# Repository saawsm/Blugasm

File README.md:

# Blugasm - A Bluetooth enabled Nogasm

This project aims to predict and detect orgasms by using a pressure sensor (and optionally, additional I2C sensors such as SpO2 and/or GSR sensor) while controlling a vibrator.

The original design and concept comes from the [nogasm](https://github.com/nogasm/nogasm). It improves upon it by making it battery operated and Bluetooth enabled, thanks to the ESP-32 microcontroller.

## Acknowledgements
The design of this board was inspired/based off the [nogasm board](https://github.com/nogasm/nogasm).

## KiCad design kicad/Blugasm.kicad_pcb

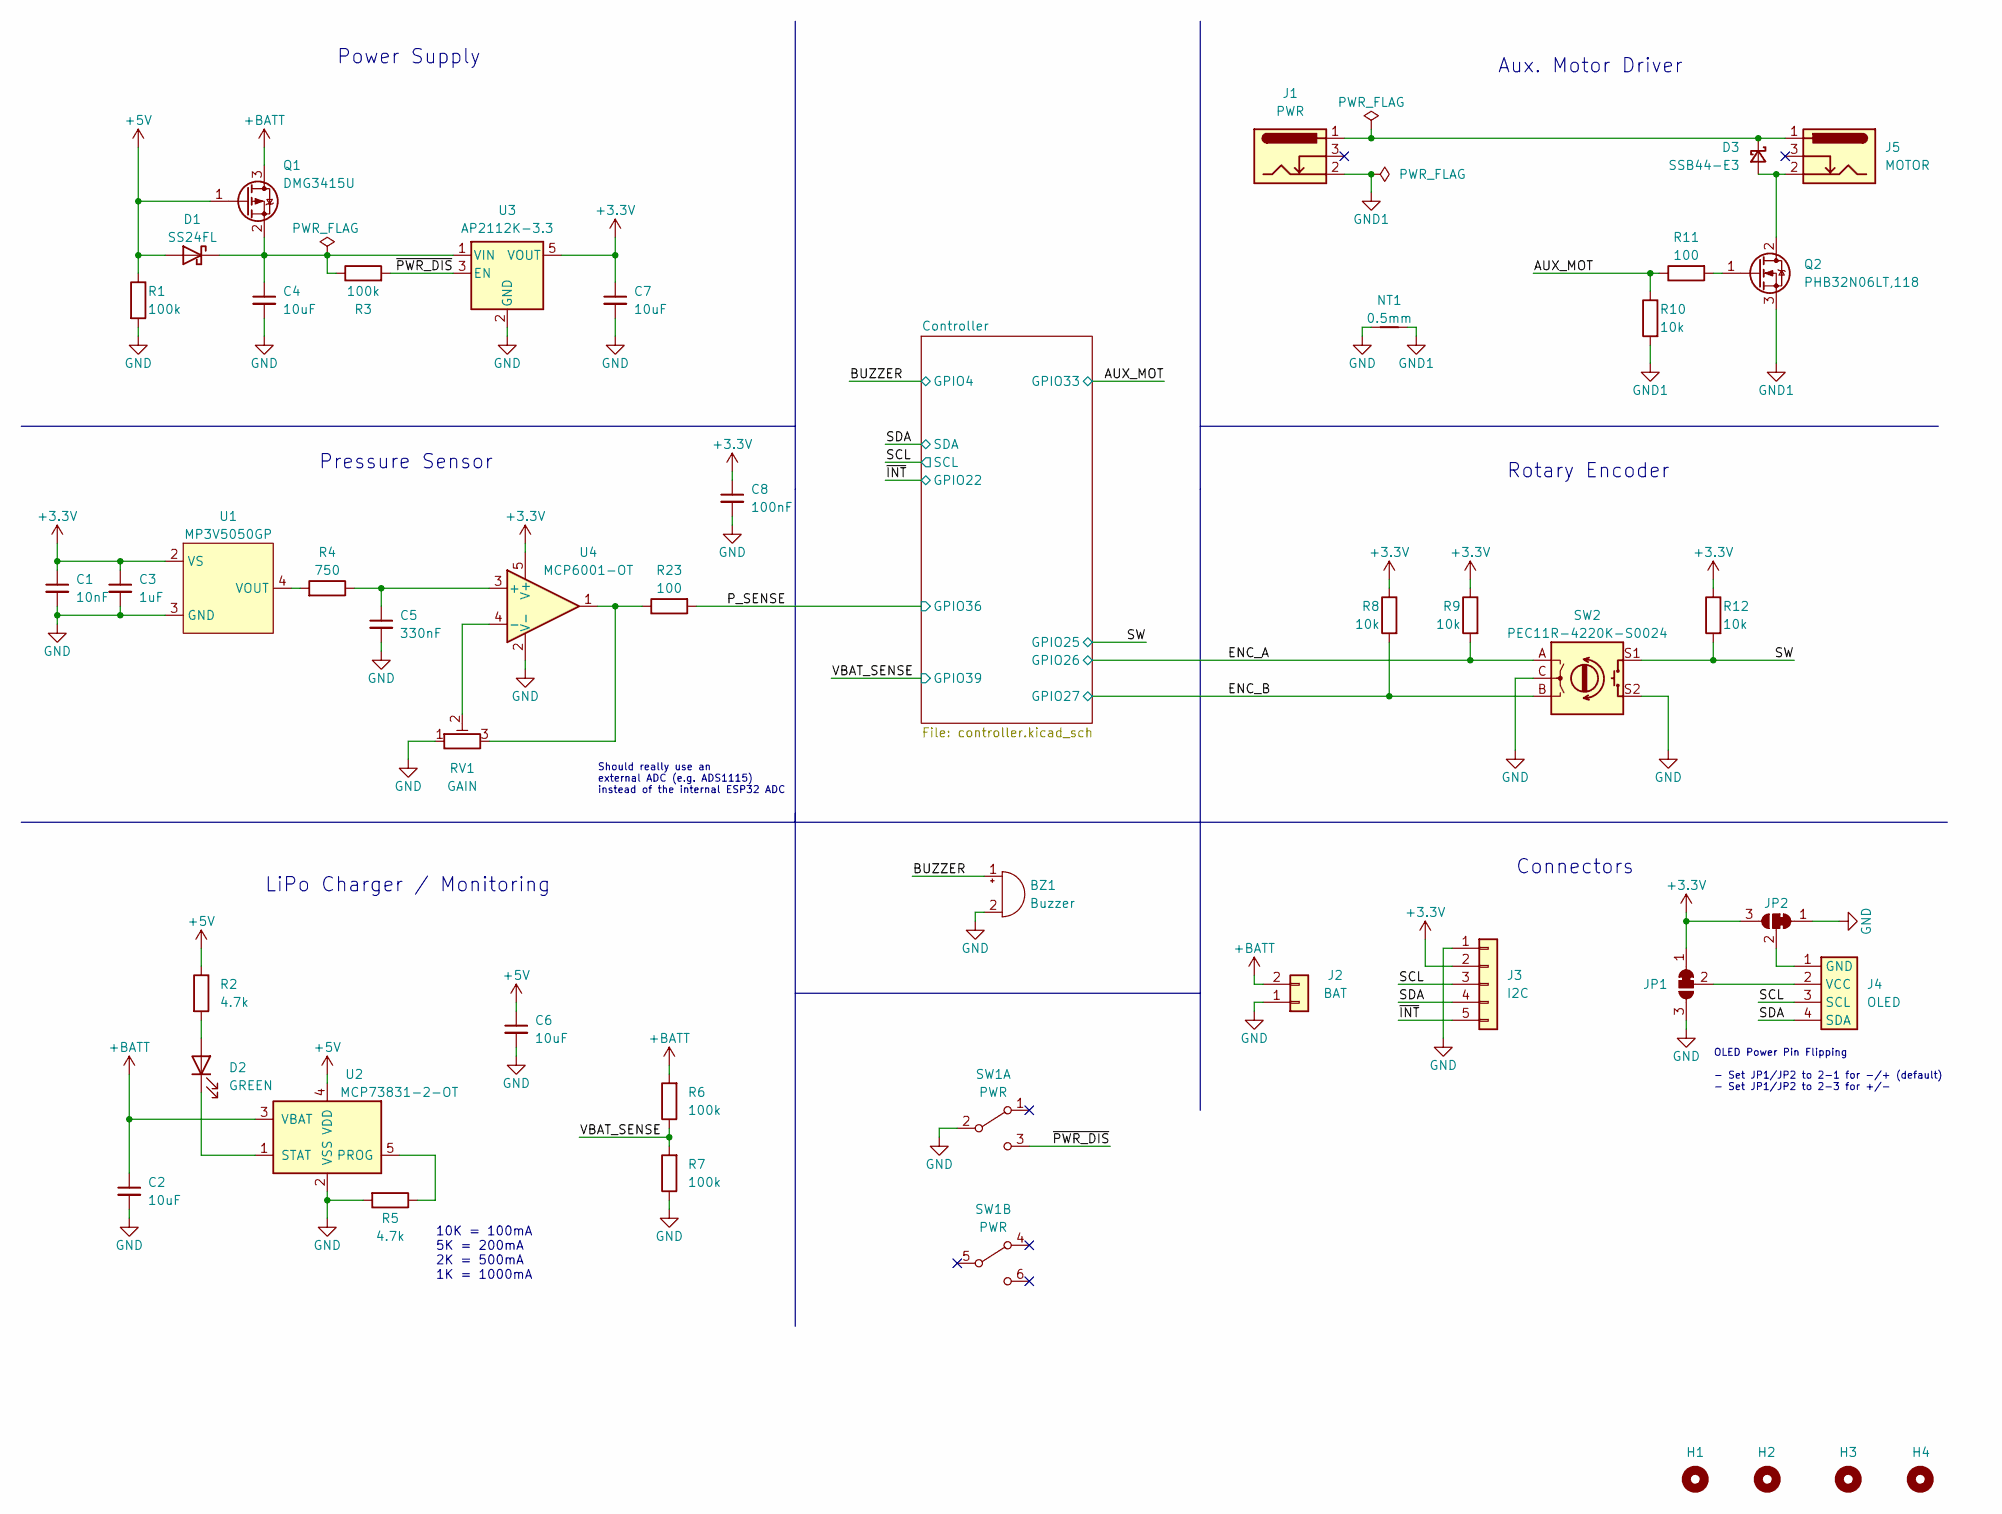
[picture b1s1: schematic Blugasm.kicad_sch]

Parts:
BZ1: Buzzer; Buzzer_12x9.5RM7.6; MPN IE122303-1; MOUSER 497-IE122303-1
C1: 10nF; C_0603_1608Metric; MPN CL10B103KB8NNNC; LCSC C1589
C2, C4, C6, C7: 10uF; C_0603_1608Metric; MPN CL10A106MA8NRNC; LCSC C96446
C3: 1uF; C_0603_1608Metric; MPN CL10B105KA8NFNC; LCSC C307479
C5: 330nF; C_0603_1608Metric; MPN CL10B334KO8NNNC; LCSC C159798
C8: 100nF; C_0603_1608Metric; MPN CL10B104KB8NNWC; LCSC C1591
D1: SS24FL; D_SOD-123F; MPN SS24FL; LCSC C894433
D2: GREEN; LED_0603_1608Metric; MPN 150060VS75000; MOUSER 710-150060VS75000
D3: SSB44-E3; D_SMB; MPN SSB44-E3/52T; LCSC C466999
H1, H2, H3, H4: MountingHole; MountingHole_2.2mm_M2
J1: PWR; BarrelJack_CUI_PJ-102AH_Horizontal; MPN PJ-102AH; MOUSER 490-PJ-102AH
J2: BAT; JST_PH_B2B-PH-K_1x02_P2.00mm_Vertical
J3: I2C; PinHeader_1x05_P2.54mm_Horizontal
J4: OLED; OLED_I2C
J5: MOTOR; BarrelJack_CUI_PJ-102AH_Horizontal; MPN PJ-102AH; MOUSER 490-PJ-102AH
JP1, JP2: SolderJumper_3_Bridged12; SolderJumper-3_P1.3mm_Bridged12_Pad1.0x1.5mm_NumberLabels
NT1: 0.5mm; NetTie-2_SMD_Pad0.5mm
Q1: DMG3415U; SOT-23; MPN DMG3415UQ-7; LCSC C459537
Q2: PHB32N06LT,118; TO-263-3_TabPin2; MPN PHB32N06LT,118; LCSC C552626
R1, R3, R6, R7: 100k; R_0603_1608Metric; MPN RC0603FR-07100KL; LCSC C14675
R2, R5: 4.7k; R_0603_1608Metric; MPN RC0603FR-074K7L; LCSC C99782
R4: 750; R_0603_1608Metric; MPN RC0603FR-07750RL; LCSC C114635
R8, R9, R10, R12: 10k; R_0603_1608Metric; MPN RC0603FR-0710KL; LCSC C98220
R11, R23: 100; R_0603_1608Metric; MPN RC0603FR-07100RL; LCSC C105588
RV1: GAIN; ST-4EB; MPN ST-4ETB103; LCSC C2922095
SW1: PWR; SW_E-Switch_EG2219_DPDT_Angled; MPN EG2219; MOUSER 612-EG2219
SW2: PEC11R-4220K-S0024; Rotary_Encoder_Switched_PEC11R; MPN PEC11R-4220K-S0024; MOUSER 652-PEC11R-4220K-S24
U1: MP3V5050GP; MP3V5050; MPN MP3V5050GP; MOUSER 841-MP3V5050GP
U2: MCP73831-2-OT; SOT-23-5; MPN MCP73831T-2ACI/OT; LCSC C424093
U3: AP2112K-3.3; SOT-23-5; MPN AP2112K-3.3TRG1; LCSC C51118
U4: MCP6001-OT; SOT-23-5; MPN MCP6001RT-I/OT; MOUSER 579-MCP6001RT-I/OT

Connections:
+3.3V: C1.1, C3.1, C7.1, C8.1, J3.2, JP1.1 (A), JP2.3 (B), R8.1, R9.1, R12.1, U1.2 (VS), U3.5 (VOUT), U4.5 (V+); also elsewhere on the board
+5V: C6.1, D1.2 (A), Q1.1 (G), R1.1, R2.1, U2.4 (VDD); also elsewhere on the board
+BATT: C2.1, J2.2, Q1.3 (D), R6.2, U2.3 (VBAT)
/AUX_MOT: R10.1, R11.1; also elsewhere on the board
/BUZZER: BZ1.1 (-); also elsewhere on the board
/ENC_A: R9.2, SW2.A; also elsewhere on the board
/ENC_B: R8.2, SW2.B; also elsewhere on the board
/P_SENSE: R23.2; also elsewhere on the board
/SCL: J3.3, J4.3 (SCL); also elsewhere on the board
/SDA: J3.4, J4.4 (SDA); also elsewhere on the board
/SW: R12.2, SW2.S1; also elsewhere on the board
/VBAT_SENSE: R6.1, R7.2; also elsewhere on the board
/~INT: J3.5; also elsewhere on the board
/~PWR_DIS: R3.2, SW1.3 (C), U3.3 (EN)
GND: BZ1.2 (+), C1.2, C2.2, C3.2, C4.2, C5.2, C6.2, C7.2, C8.2, J2.1, J3.1, JP1.3 (B), JP2.1 (A), NT1.1, R1.2, R5.2, R7.1, RV1.1, SW1.2 (B), SW2.C, SW2.S2, U1.3 (GND), U2.2 (VSS), U3.2 (GND), U4.2 (V-); also elsewhere on the board
GND1: J1.2, NT1.2, Q2.3 (S), R10.2
unnamed: C4.1, D1.1 (K), Q1.2 (S), R3.1, U3.1 (VIN)
unnamed: C5.1, R4.1, U4.3 (+)
unnamed: D2.1 (K), U2.1 (STAT)
unnamed: D2.2 (A), R2.2
unnamed: D3.1 (K), J1.1, J5.1
unnamed: D3.2 (A), J5.2, Q2.2 (D)
unnamed: J4.1 (GND), JP2.2 (C)
unnamed: J4.2 (VCC), JP1.2 (C)
unnamed: Q2.1 (G), R11.2
unnamed: R4.2, U1.4 (VOUT)
unnamed: R5.1, U2.5 (PROG)
unnamed: R23.1, RV1.3, U4.1
unnamed: RV1.2, U4.4 (-)

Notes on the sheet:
Should really use an external ADC (e.g. ADS1115) instead of the internal ESP32 ADC
Aux. Motor Driver
Connectors
OLED Power Pin Flipping - Set JP1/JP2 to 2-1 for -/+ (default) - Set JP1/JP2 to 2-3 for +/-
10K = 100mA 5K = 200mA 2K = 500mA 1K = 1000mA
Rotary Encoder
Pressure Sensor
Power Supply
LiPo Charger / Monitoring

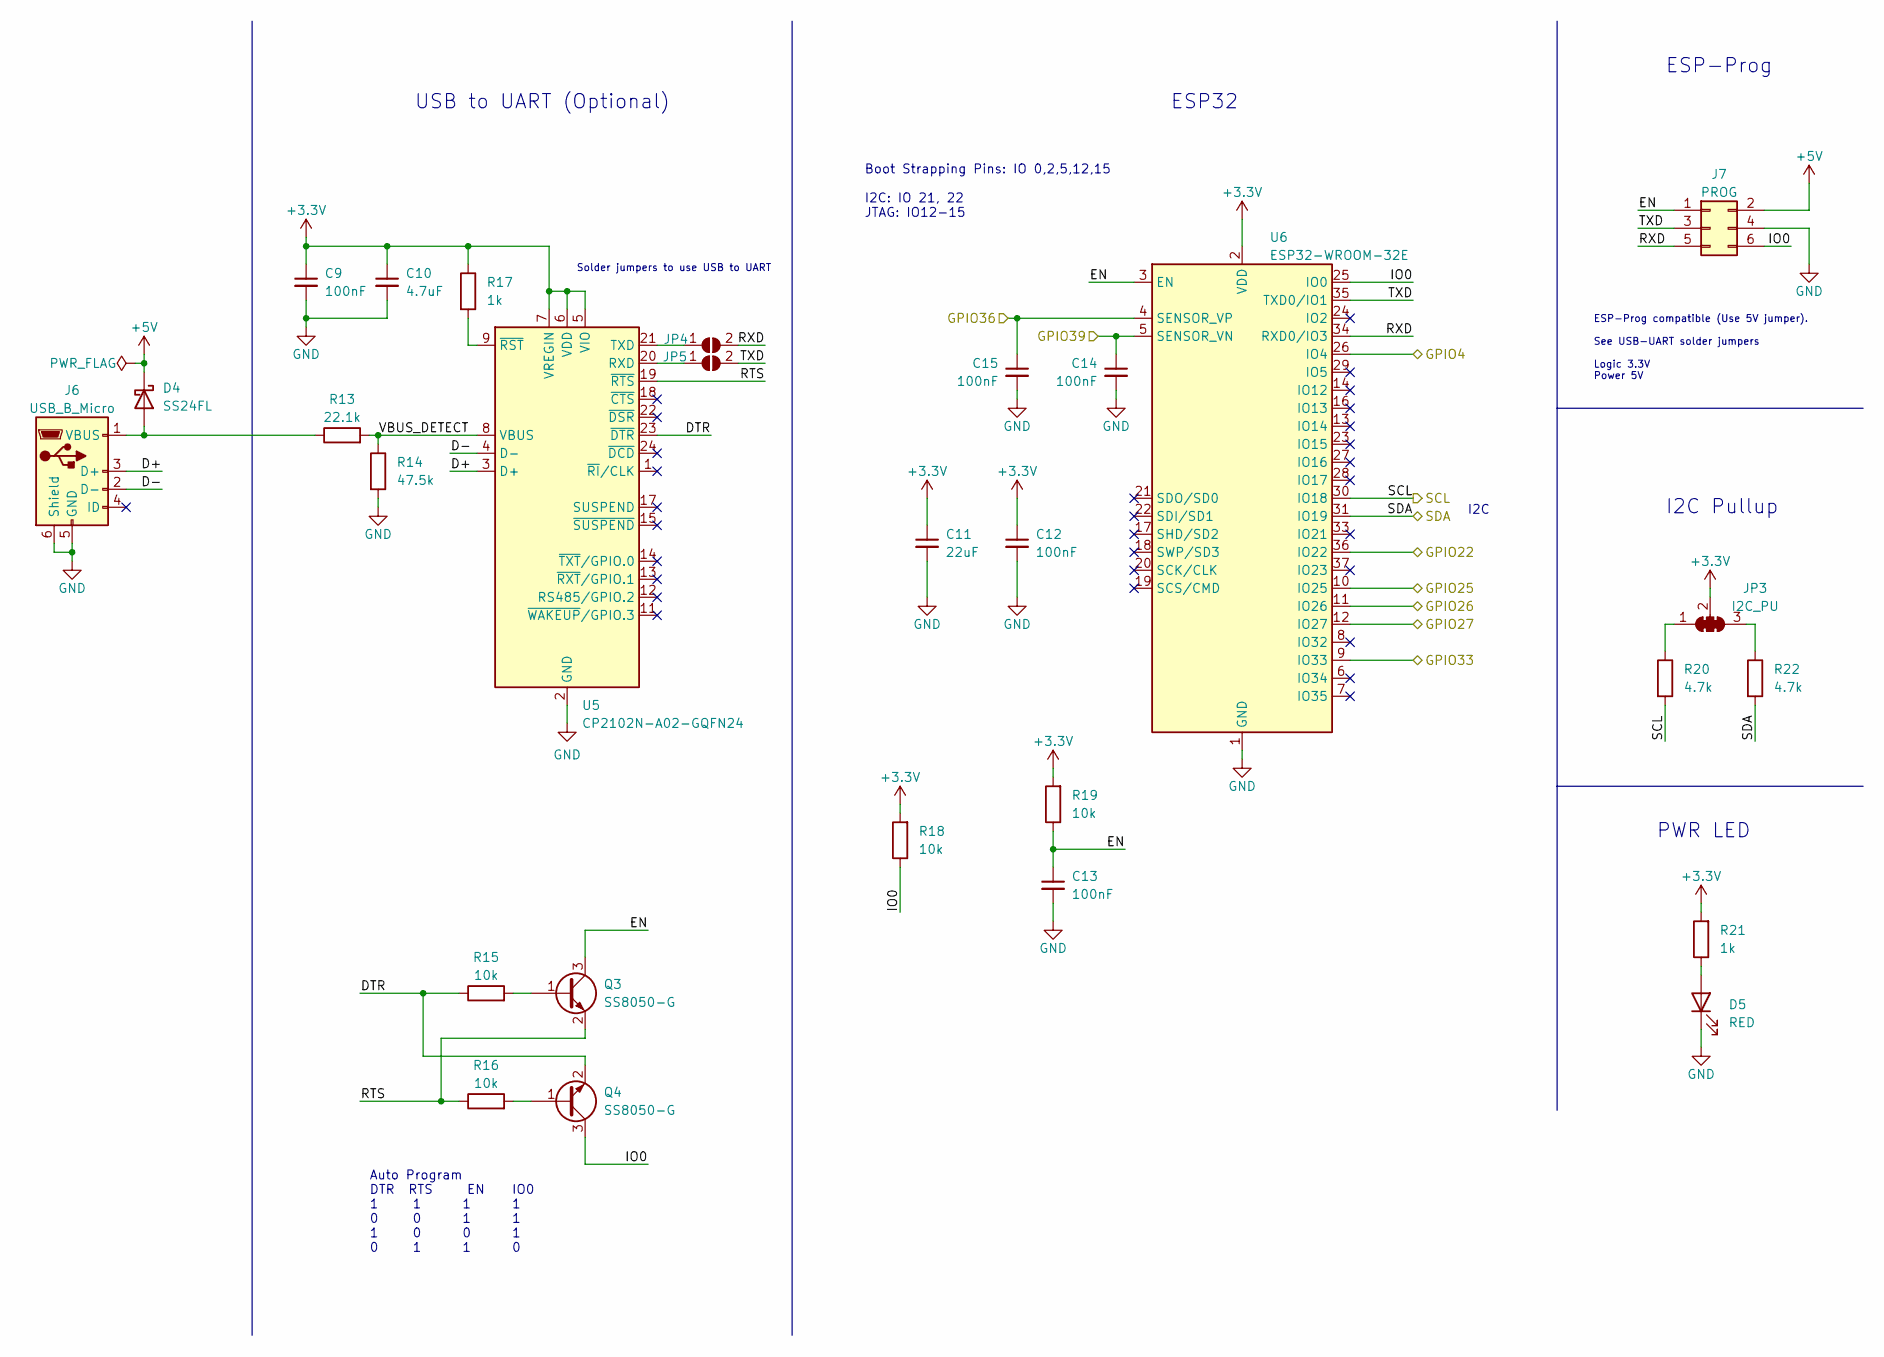
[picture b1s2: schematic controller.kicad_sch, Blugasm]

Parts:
C9, C12, C13, C14, C15: 100nF; C_0603_1608Metric; MPN CL10B104KB8NNWC; LCSC C1591
C10: 4.7uF; C_0603_1608Metric; MPN CL10A475KQ8NNWC; LCSC C3849923
C11: 22uF; C_0603_1608Metric; MPN CL10A106MA8NRNC; LCSC C96446
D4: SS24FL; D_SOD-123F; MPN SS24FL; LCSC C894433
D5: RED; LED_0603_1608Metric; MPN 150060RS75000; MOUSER 710-150060RS75000
J6: USB_B_Micro; USB_Micro-B_GCT_USB3076-30-A; MPN USB3076-30-A; MOUSER 640-USB3076-30-A
J7: PROG; IDC-Header_2x03_P2.54mm_Vertical
JP3: I2C_PU; SolderJumper-3_P1.3mm_Bridged123_Pad1.0x1.5mm_NumberLabels
JP4: UART_TXD; SolderJumper-2_P1.3mm_Open_RoundedPad1.0x1.5mm
JP5: UART_RXD; SolderJumper-2_P1.3mm_Open_RoundedPad1.0x1.5mm
Q3, Q4: SS8050-G; SOT-23; MPN SS8050-G; LCSC C164886
R13: 22.1k; R_0603_1608Metric; MPN RC0603FR-0722K1L; LCSC C137768
R14: 47.5k; R_0603_1608Metric; MPN RC0603FR-1047K5L; LCSC C4149630
R15, R16, R18, R19: 10k; R_0603_1608Metric; MPN RC0603FR-0710KL; LCSC C98220
R17, R21: 1k; R_0603_1608Metric; MPN RC0603FR-071KL; LCSC C22548
R20, R22: 4.7k; R_0603_1608Metric; MPN RC0603FR-074K7L; LCSC C99782
U5: CP2102N-A02-GQFN24; QFN-24-1EP_4x4mm_P0.5mm_EP2.6x2.6mm; MPN CP2102N-A02-GQFN24R; LCSC C969151
U6: ESP32-WROOM-32E; ESP32-WROOM-32; MPN ESP32-WROOM-32E-N16; LCSC C701343

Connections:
+3.3V: C9.1, C10.1, C11.1, C12.1, JP3.2 (C), R17.1, R18.2, R19.2, R21.2, U5.5 (VIO), U5.6 (VDD), U5.7 (VREGIN), U6.2 (VDD); also elsewhere on the board
+5V: D4.1 (K), J7.2; also elsewhere on the board
/AUX_MOT: U6.9 (IO33); also elsewhere on the board
/BUZZER: U6.26 (IO4); also elsewhere on the board
/Controller/D+: J6.3 (D+), U5.3 (D+)
/Controller/D-: J6.2 (D-), U5.4 (D-)
/Controller/DTR: Q4.2 (E), R15.1, U5.23 (~DTR)
/Controller/EN: C13.1, J7.1, Q3.3 (C), R19.1, U6.3 (EN)
/Controller/IO0: J7.6, Q4.3 (C), R18.1, U6.25 (IO0)
/Controller/RTS: Q3.2 (E), R16.1, U5.19 (~RTS)
/Controller/RXD: J7.5, JP4.2 (B), U6.34 (RXD0/IO3)
/Controller/TXD: J7.3, JP5.2 (B), U6.35 (TXD0/IO1)
/Controller/VBUS_DETECT: R13.2, R14.1, U5.8 (VBUS)
/ENC_A: U6.11 (IO26); also elsewhere on the board
/ENC_B: U6.12 (IO27); also elsewhere on the board
/P_SENSE: C15.1, U6.4 (SENSOR_VP); also elsewhere on the board
/SCL: R20.2, U6.30 (IO18); also elsewhere on the board
/SDA: R22.2, U6.31 (IO19); also elsewhere on the board
/SW: U6.10 (IO25); also elsewhere on the board
/VBAT_SENSE: C14.1, U6.5 (SENSOR_VN); also elsewhere on the board
/~INT: U6.36 (IO22); also elsewhere on the board
GND: C9.2, C10.2, C11.2, C12.2, C13.2, C14.2, C15.2, D5.1 (K), J6.5 (GND), J6.6 (Shield), J7.4, R14.2, U5.2 (GND), U5.25 (GND), U6.1 (GND), U6.15 (GND), U6.38 (GND), U6.39 (GND); also elsewhere on the board
unnamed: D4.2 (A), J6.1 (VBUS), R13.1
unnamed: D5.2 (A), R21.1
unnamed: JP3.1 (A), R20.1
unnamed: JP3.3 (B), R22.1
unnamed: JP4.1 (A), U5.21 (TXD)
unnamed: JP5.1 (A), U5.20 (RXD)
unnamed: Q3.1 (B), R15.2
unnamed: Q4.1 (B), R16.2
unnamed: R17.2, U5.9 (~RST)

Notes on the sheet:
ESP32
PWR LED
ESP-Prog
I2C Pullup
Solder jumpers to use USB to UART
I2C
USB to UART (Optional)
Boot Strapping Pins: IO 0,2,5,12,15 I2C: IO 21, 22 JTAG: IO12-15
Auto Program DTR RTS EN IO0 1 1 1 1 0 0 1 1 1 0 0 1 0 1 1 0
ESP-Prog compatible (Use 5V jumper). See USB-UART solder jumpers Logic 3.3V Power 5V

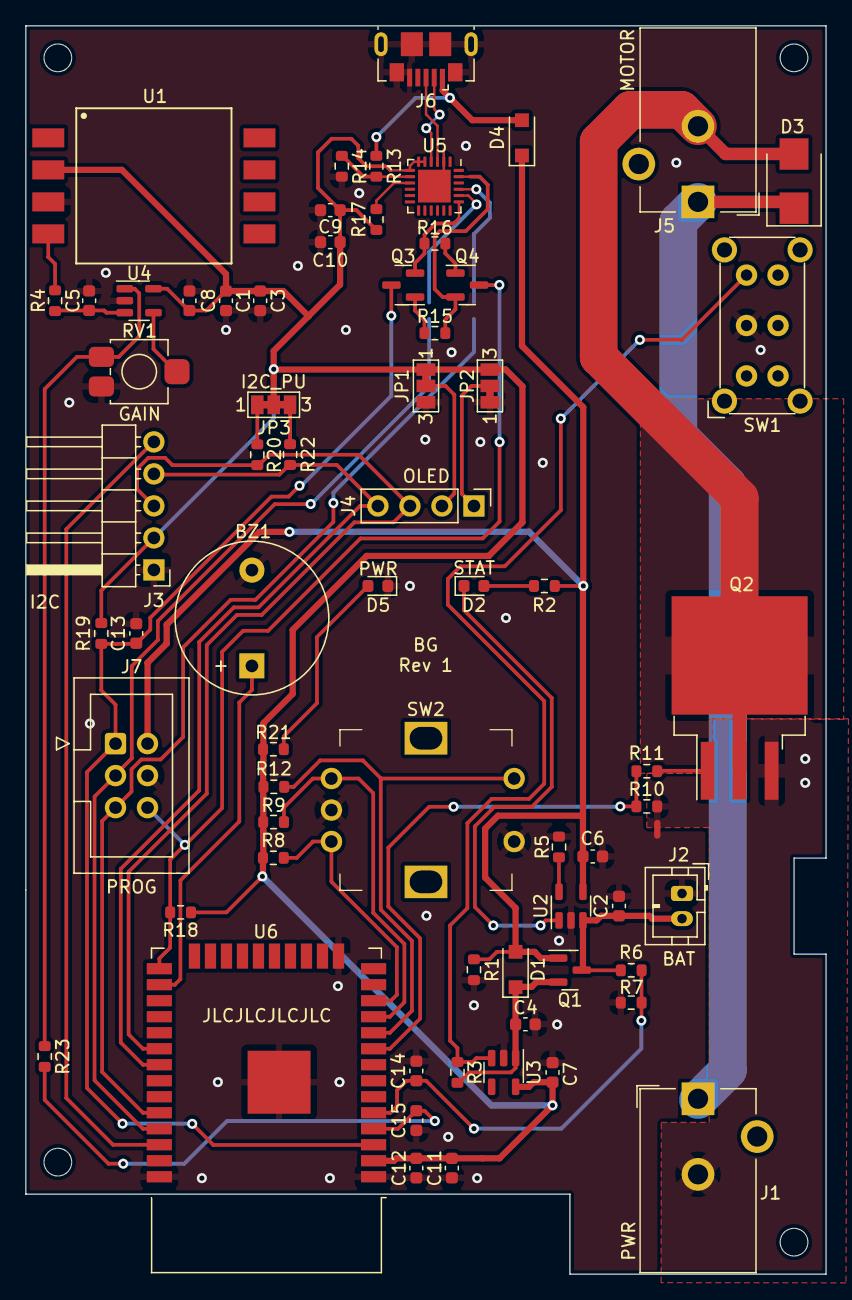
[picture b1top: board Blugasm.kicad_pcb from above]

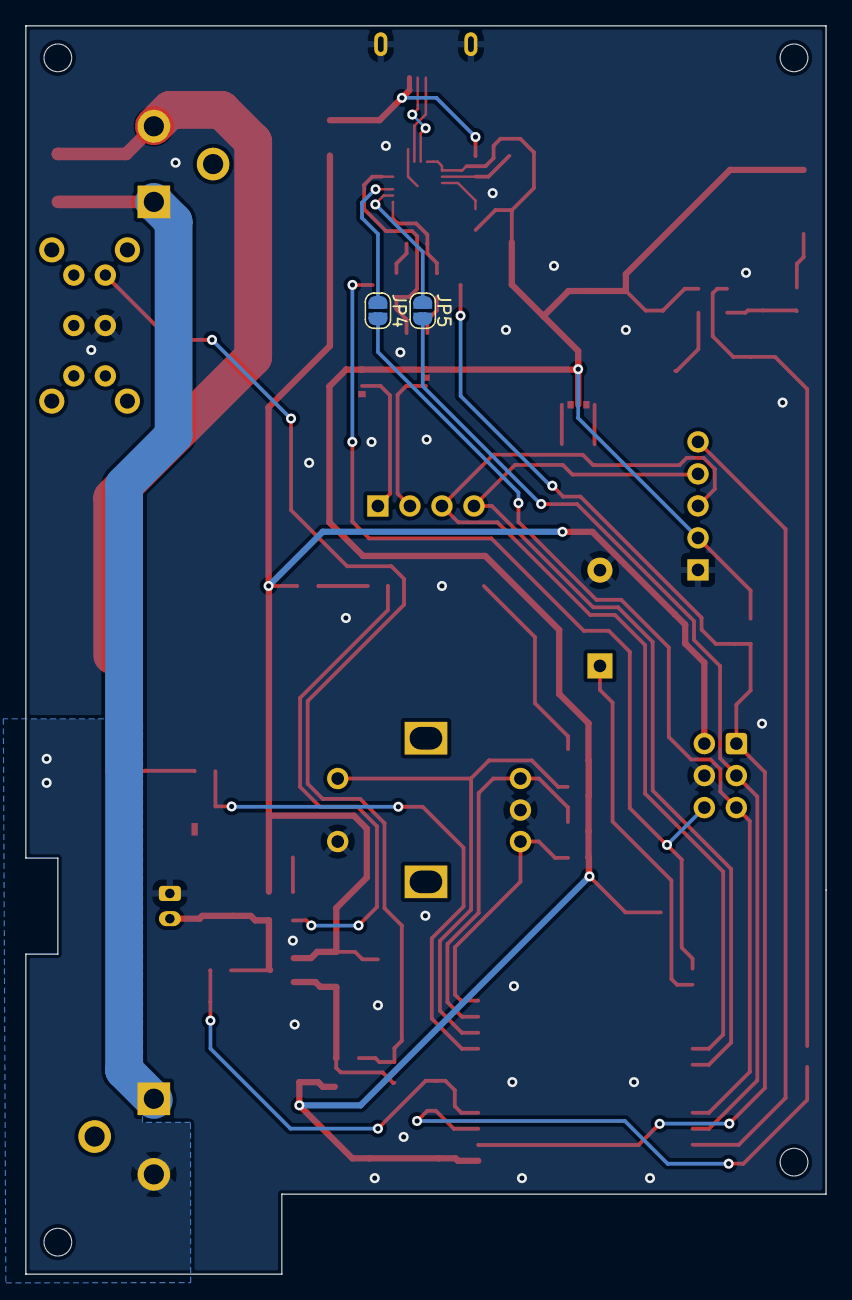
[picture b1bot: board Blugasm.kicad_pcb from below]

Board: 2 copper layers, 63.5 x 99.1 mm, 74 parts (2 on the bottom side), 47 nets.

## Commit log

2022-01-31 move to pcb folder
2022-01-31 add template project
2022-01-31 add schematic pdf
2022-02-02 assign footprints
2022-02-02 update dru
2022-11-14 cleanup
2023-01-17 add pcb
2023-01-24 fix incorrect footprint
2023-02-04 use sensor_vp/vn for ADC
2023-06-29 add LICENSE
2024-05-21 add image preview
